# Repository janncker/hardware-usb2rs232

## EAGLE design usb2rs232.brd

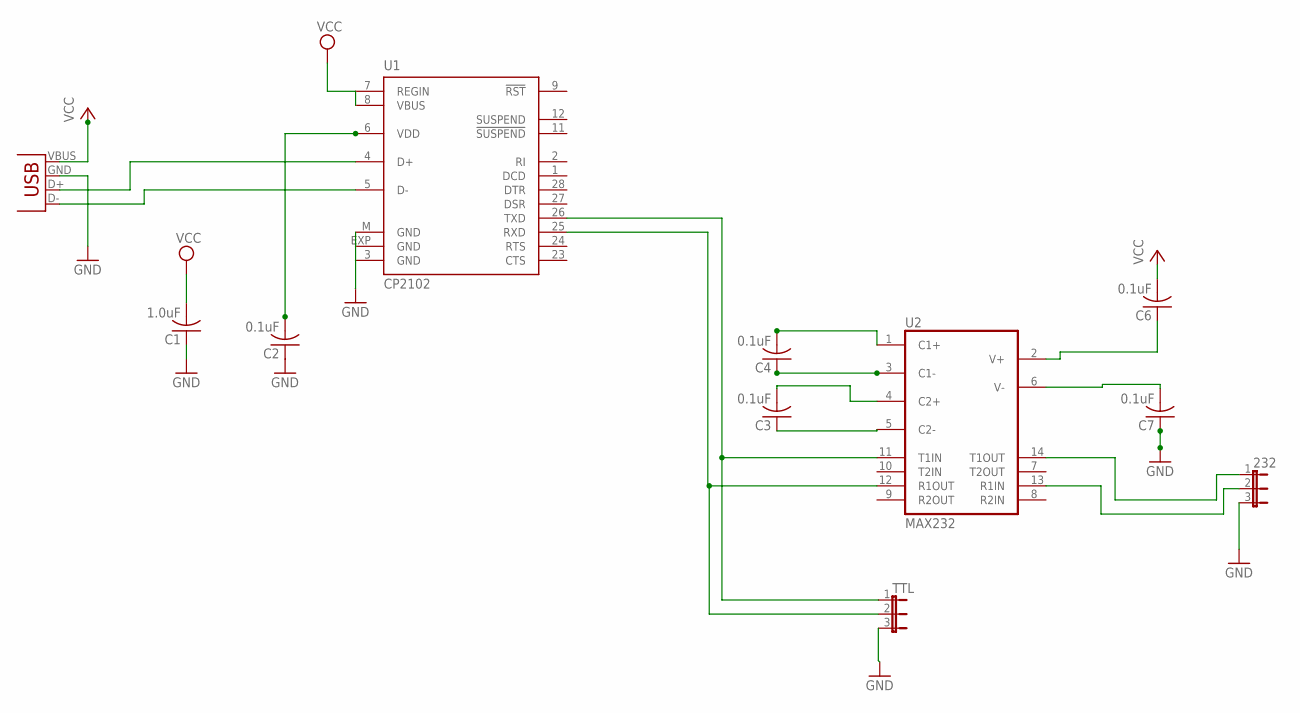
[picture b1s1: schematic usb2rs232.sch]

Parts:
232: JP2E; JP2
C1: 1.0uF; C0603
C2, C3, C4, C6, C7: 0.1uF; C0603
JP3: USB-A-H
TTL: JP2E; JP2
U1: CP2102; MLP28
U2: MAX232; SO16

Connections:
GND: 232.3, C1.1, C2.1, C7.1, JP3.GND (VBUS), TTL.3, U1.3 (GND), U1.EXP (GND), U1.M (GND), U2.15 (GND)
unnamed: TTL.1, U1.26 (TXD), U2.11 (T1IN)
unnamed: C4.2, U2.1 (C1+)
unnamed: C4.1, U2.3 (C1-)
unnamed: JP3.D+ (D-), U1.4 (D+)
unnamed: JP3.D- (D+), U1.5 (D-)
unnamed: C3.2, U2.4 (C2+)
unnamed: C3.1, U2.5 (C2-)
unnamed: C6.1, U2.2 (V+)
unnamed: C7.2, U2.6 (V-)
unnamed: 232.1, U2.14 (T1OUT)
unnamed: 232.2, U2.13 (R1IN)
unnamed: C2.2, U1.6 (VDD)
unnamed: TTL.2, U1.25 (RXD), U2.12 (R1OUT)
VCC: C1.2, C6.2, JP3.VBUS (GND), U1.7 (REGIN), U1.8 (VBUS), U2.16 (VCC)

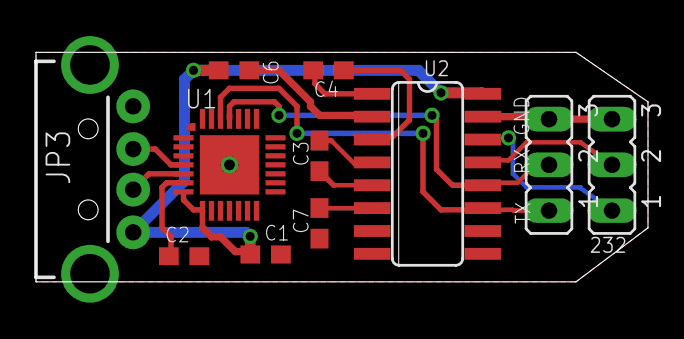
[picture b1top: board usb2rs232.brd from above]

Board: 2 copper layers, 34.0 x 12.8 mm, 11 parts (0 on the bottom side), 15 nets.

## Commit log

2014-03-06 init commit
2014-03-07 Fix CP2102 package issues
2014-03-17 modify CP2012 for manual soldering

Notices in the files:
parts and their libraries:
SparkFun-Connectors: Licensing: Creative Commons ShareAlike 4.0 International - https://creativecommons.org/licenses/by-sa/4.0
